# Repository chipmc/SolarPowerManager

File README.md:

# SolarPowerManager
Solar Power v2c Files
This is a Solar Power Manager.  See full product description at www.hackster.io/chipmc

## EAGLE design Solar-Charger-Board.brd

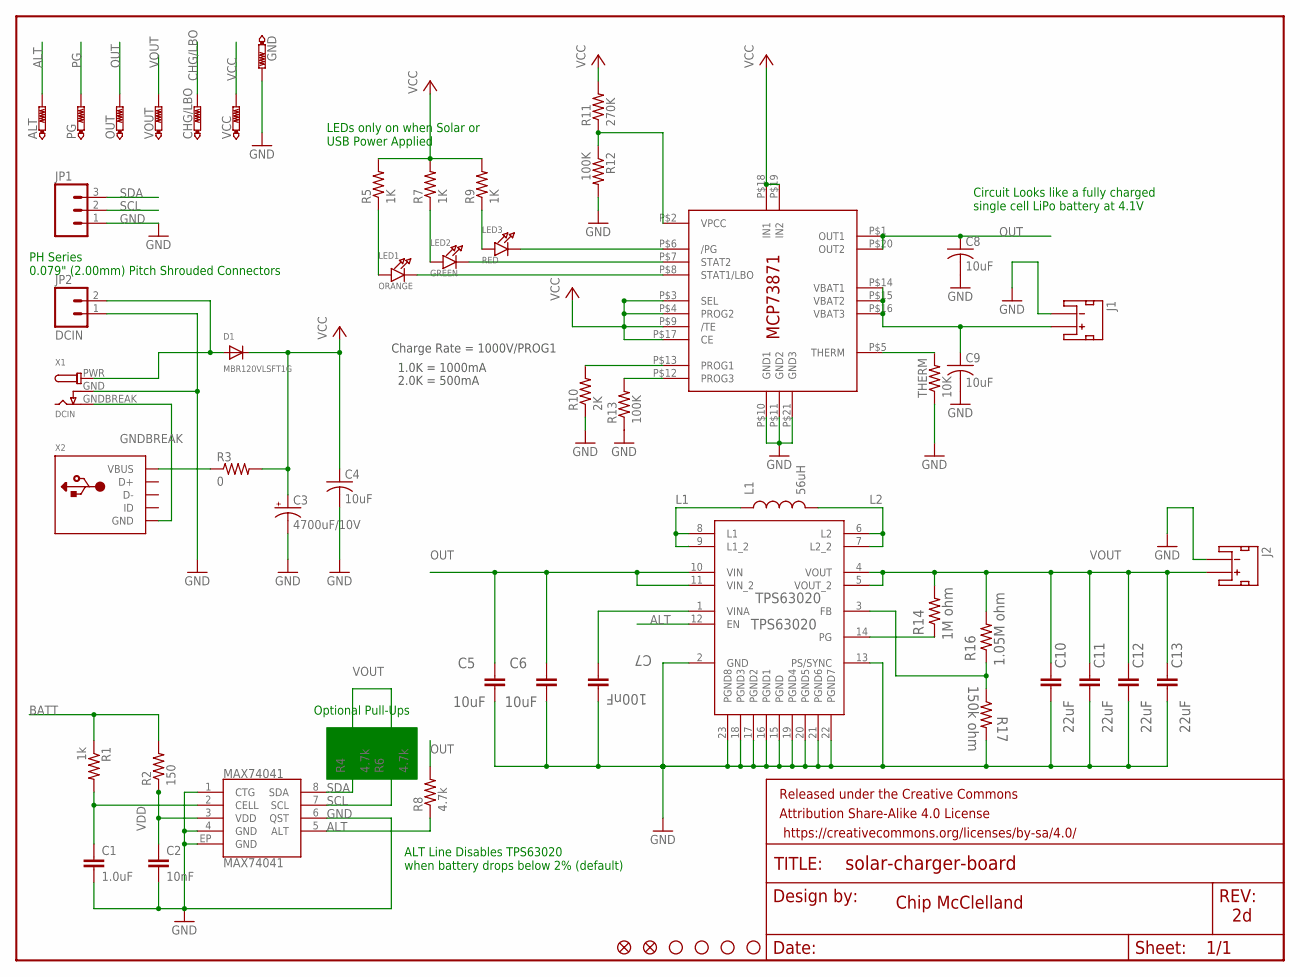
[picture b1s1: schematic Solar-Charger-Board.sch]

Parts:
ALT: PTR1TP09R; TP09R
C1: 1.0uF; 0805
C2: 10nF; 0805
C3: 4700uF/10V; E5-13
C4, C8, C9: 10uF; C0805K
C5, C6: 10uF; 0805
C7: 100nF; 0805
C10, C11, C12, C13: 22uF; 0805
CHG/LBO: PTR1TP09R; TP09R
D1: MBR120VLSFT1G; SOD-123
FID1, FID2: FIDUCIALUFIDUCIAL; MICRO-FIDUCIAL
FRAME1: FRAME-LETTER; CREATIVE_COMMONS
GND: PTR1TP09R; TP09R
J1, J2: JST_2MM_MALE; JST-2-SMD
JP1: M03LOCK; 1X03_LOCK
JP2: DCIN; 1X02_LOCK
JP3, JP4, JP5, JP6: STAND-OFF
L1: 56uH; SDR0403
LED1: ORANGE; CHIPLED_0805_NOOUTLINE
LED2: GREEN; CHIPLED_0805_NOOUTLINE
LED3: RED; CHIPLED_0805_NOOUTLINE
MAX74041: MAX74041; TDFN-8
MCP73871: U1; QFN20_4MM
OUT: PTR1TP09R; TP09R
PG: PTR1TP09R; TP09R
R1: 1k; 0805
R2: 150; 0805
R3: 0; 0805
R4, R6, R8: 4.7k; 0805
R5, R7, R9: 1K; 0805
R10: 2K; 0805
R11: 270K; 0805
R12, R13: 100K; 0805
R14: 1M ohm; 0805
R16: 1.05M ohm; 0805
R17: 150k ohm; 0805
THERM: 10K; 0805
TPS63020: TPS63020; QFN14-3X4MM
VCC: PTR1TP09R; TP09R
VOUT: PTR1TP09R; TP09R
X1: DCIN; DCJACK_2MM_SMT
X2: USBMINIBLARGE; USB-MINIB_LARGER

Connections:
ALT: ALT.TP, MAX74041.5 (ALT), R8.1, TPS63020.12 (EN)
BATT: C9.1, J1.2 (+), MCP73871.P$14 (VBAT1), MCP73871.P$15 (VBAT2), MCP73871.P$16 (VBAT3), R1.1, R2.2
CHG/LBO: CHG/LBO.TP, LED1.C, MCP73871.P$8 (STAT1/LBO)
DC-IN: D1.A, JP2.2, X1.PWR
DONE: LED2.C, MCP73871.P$7 (STAT2)
FB: R16.1, R17.1, TPS63020.3 (FB)
GND: C1.2, C2.2, C3.-, C4.2, C5.2, C6.2, C7.2, C8.2, C9.2, C10.2, C11.2, C12.2, C13.2, GND.TP, J1.1 (-), J2.1 (-), JP1.1, JP2.1, MAX74041.1 (CTG), MAX74041.4 (GND), MAX74041.6 (QST), MAX74041.EP (GND), MCP73871.P$10 (GND1), MCP73871.P$11 (GND2), MCP73871.P$21 (GND3), R10.1, R12.2, R13.1, R17.2, THERM.1, TPS63020.2 (GND), TPS63020.13 (PS/SYNC), TPS63020.15 (PGND), TPS63020.16 (PGND1), TPS63020.17 (PGND2), TPS63020.18 (PGND3), TPS63020.19 (PGND4), TPS63020.20 (PGND5), TPS63020.21 (PGND6), TPS63020.22 (PGND7), TPS63020.23 (PGND8), X1.GND (GNDBREAK)
GNDBREAK: X1.GNDBREAK (GND), X2.GND, X2.GND1 (GND), X2.GND2 (GND), X2.GND3 (GND), X2.GND4 (GND)
L1: L1.P$1 (1), TPS63020.8 (L1), TPS63020.9 (L1_2)
L2: L1.P$2 (2), TPS63020.6 (L2), TPS63020.7 (L2_2)
unnamed: C1.1, MAX74041.2 (CELL), R1.2
unnamed: MCP73871.P$2 (VPCC), R11.1, R12.1
unnamed: C7.1, TPS63020.1 (VINA)
unnamed: MCP73871.P$5 (THERM), THERM.2
unnamed: LED1.A, R5.1
unnamed: LED2.A, R7.1
unnamed: LED3.A, R9.1
unnamed: MCP73871.P$12 (PROG3), R13.2
unnamed: MCP73871.P$13 (PROG1), R10.2
OUT: C5.1, C6.1, C8.1, MCP73871.P$1 (OUT1), MCP73871.P$20 (OUT2), OUT.TP, R8.2, TPS63020.10 (VIN), TPS63020.11 (VIN_2)
PG: PG.TP, R14.1, TPS63020.14 (PG)
PWR: LED3.C, MCP73871.P$6 (/PG)
SCL: JP1.2, MAX74041.7 (SCL), R6.1
SDA: JP1.3, MAX74041.8 (SDA), R4.1
VBUS: R3.1, X2.VBUS
VCC: C3.+, C4.1, D1.C, MCP73871.P$3 (SEL), MCP73871.P$4 (PROG2), MCP73871.P$9 (/TE), MCP73871.P$17 (CE), MCP73871.P$18 (IN1), MCP73871.P$19 (IN2), R3.2, R5.2, R7.2, R9.2, R11.2, VCC.TP
VDD: C2.1, MAX74041.3 (VDD), R2.1
VOUT: C10.1, C11.1, C12.1, C13.1, J2.2 (+), R4.2, R6.2, R14.2, R16.2, TPS63020.4 (VOUT), TPS63020.5 (VOUT_2), VOUT.TP

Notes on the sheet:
Charge Rate = 1000V/PROG1
1.0K = 1000mA
2.0K = 500mA
Chip McClelland
Optional Pull-Ups
ALT Line Disables TPS63020 when battery drops below 2% (default)
LEDs only on when Solar or USB Power Applied
Circuit Looks like a fully charged single cell LiPo battery at 4.1V
PH Series 0.079" (2.00mm) Pitch Shrouded Connectors

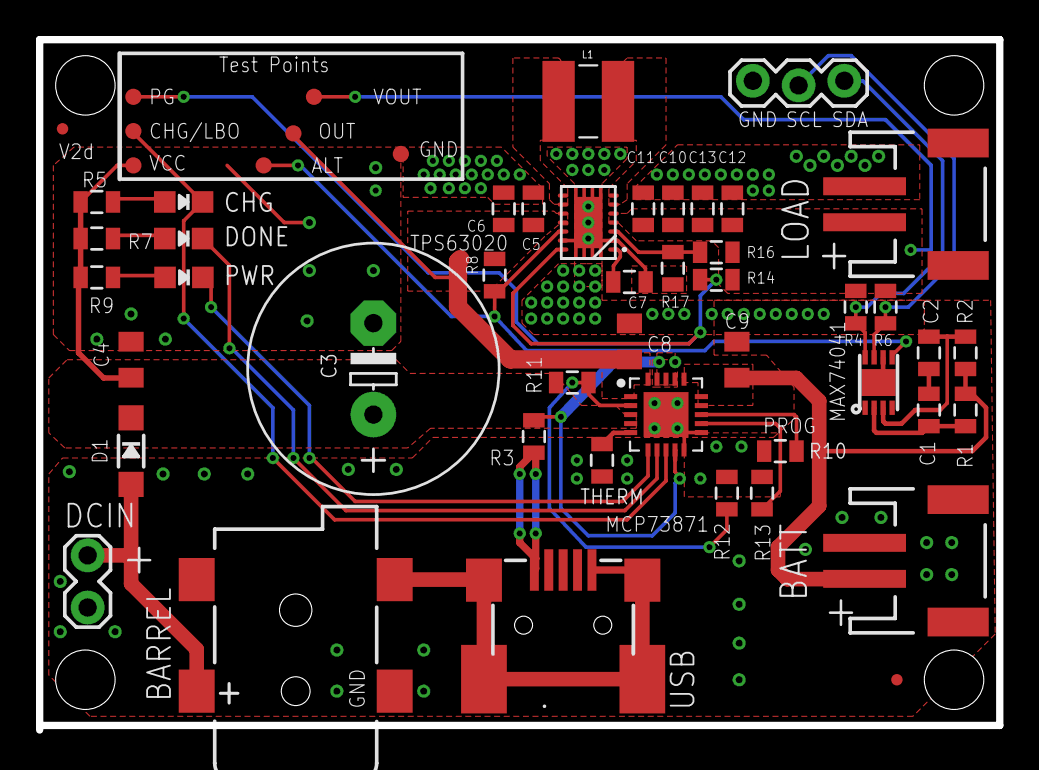
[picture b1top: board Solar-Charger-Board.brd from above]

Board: 2 copper layers, 53.3 x 38.4 mm, 58 parts (0 on the bottom side), 28 nets.

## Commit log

2017-05-08 EAGLE CAD Files
    Made using v8

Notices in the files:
parts and their libraries:
SparkFun-Connectors: Licensing: Creative Commons ShareAlike 4.0 International - https://creativecommons.org/licenses/by-sa/4.0
SparkFun-Aesthetics: Released under the Creative Commons Attribution Share-Alike 4.0 License
SparkFun-Aesthetics: https://creativecommons.org/licenses/by-sa/4.0
